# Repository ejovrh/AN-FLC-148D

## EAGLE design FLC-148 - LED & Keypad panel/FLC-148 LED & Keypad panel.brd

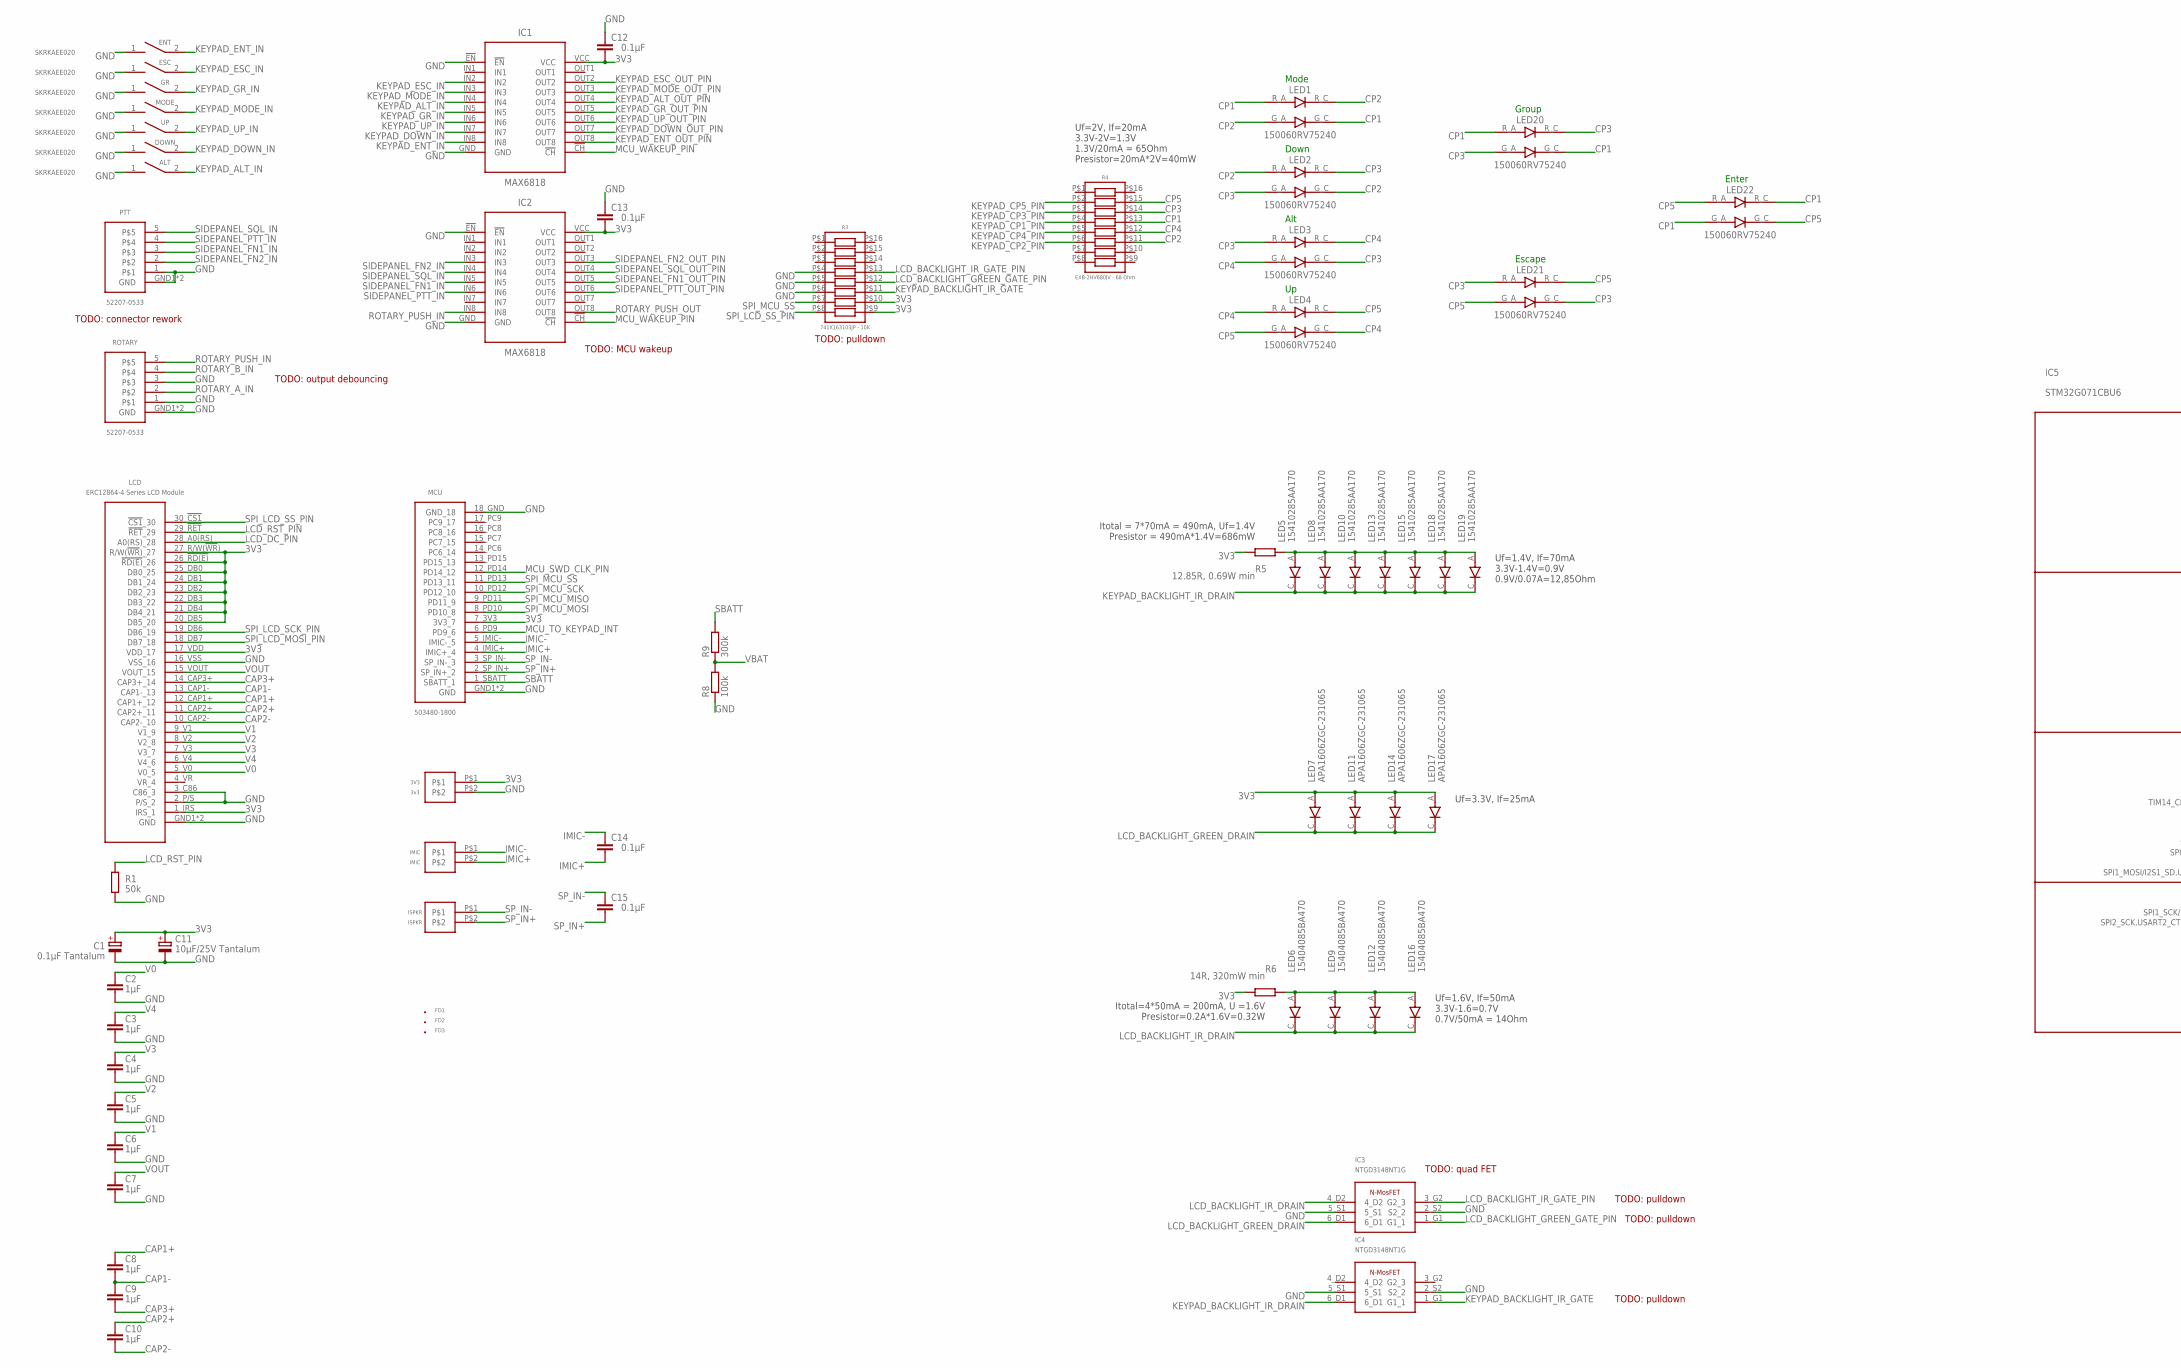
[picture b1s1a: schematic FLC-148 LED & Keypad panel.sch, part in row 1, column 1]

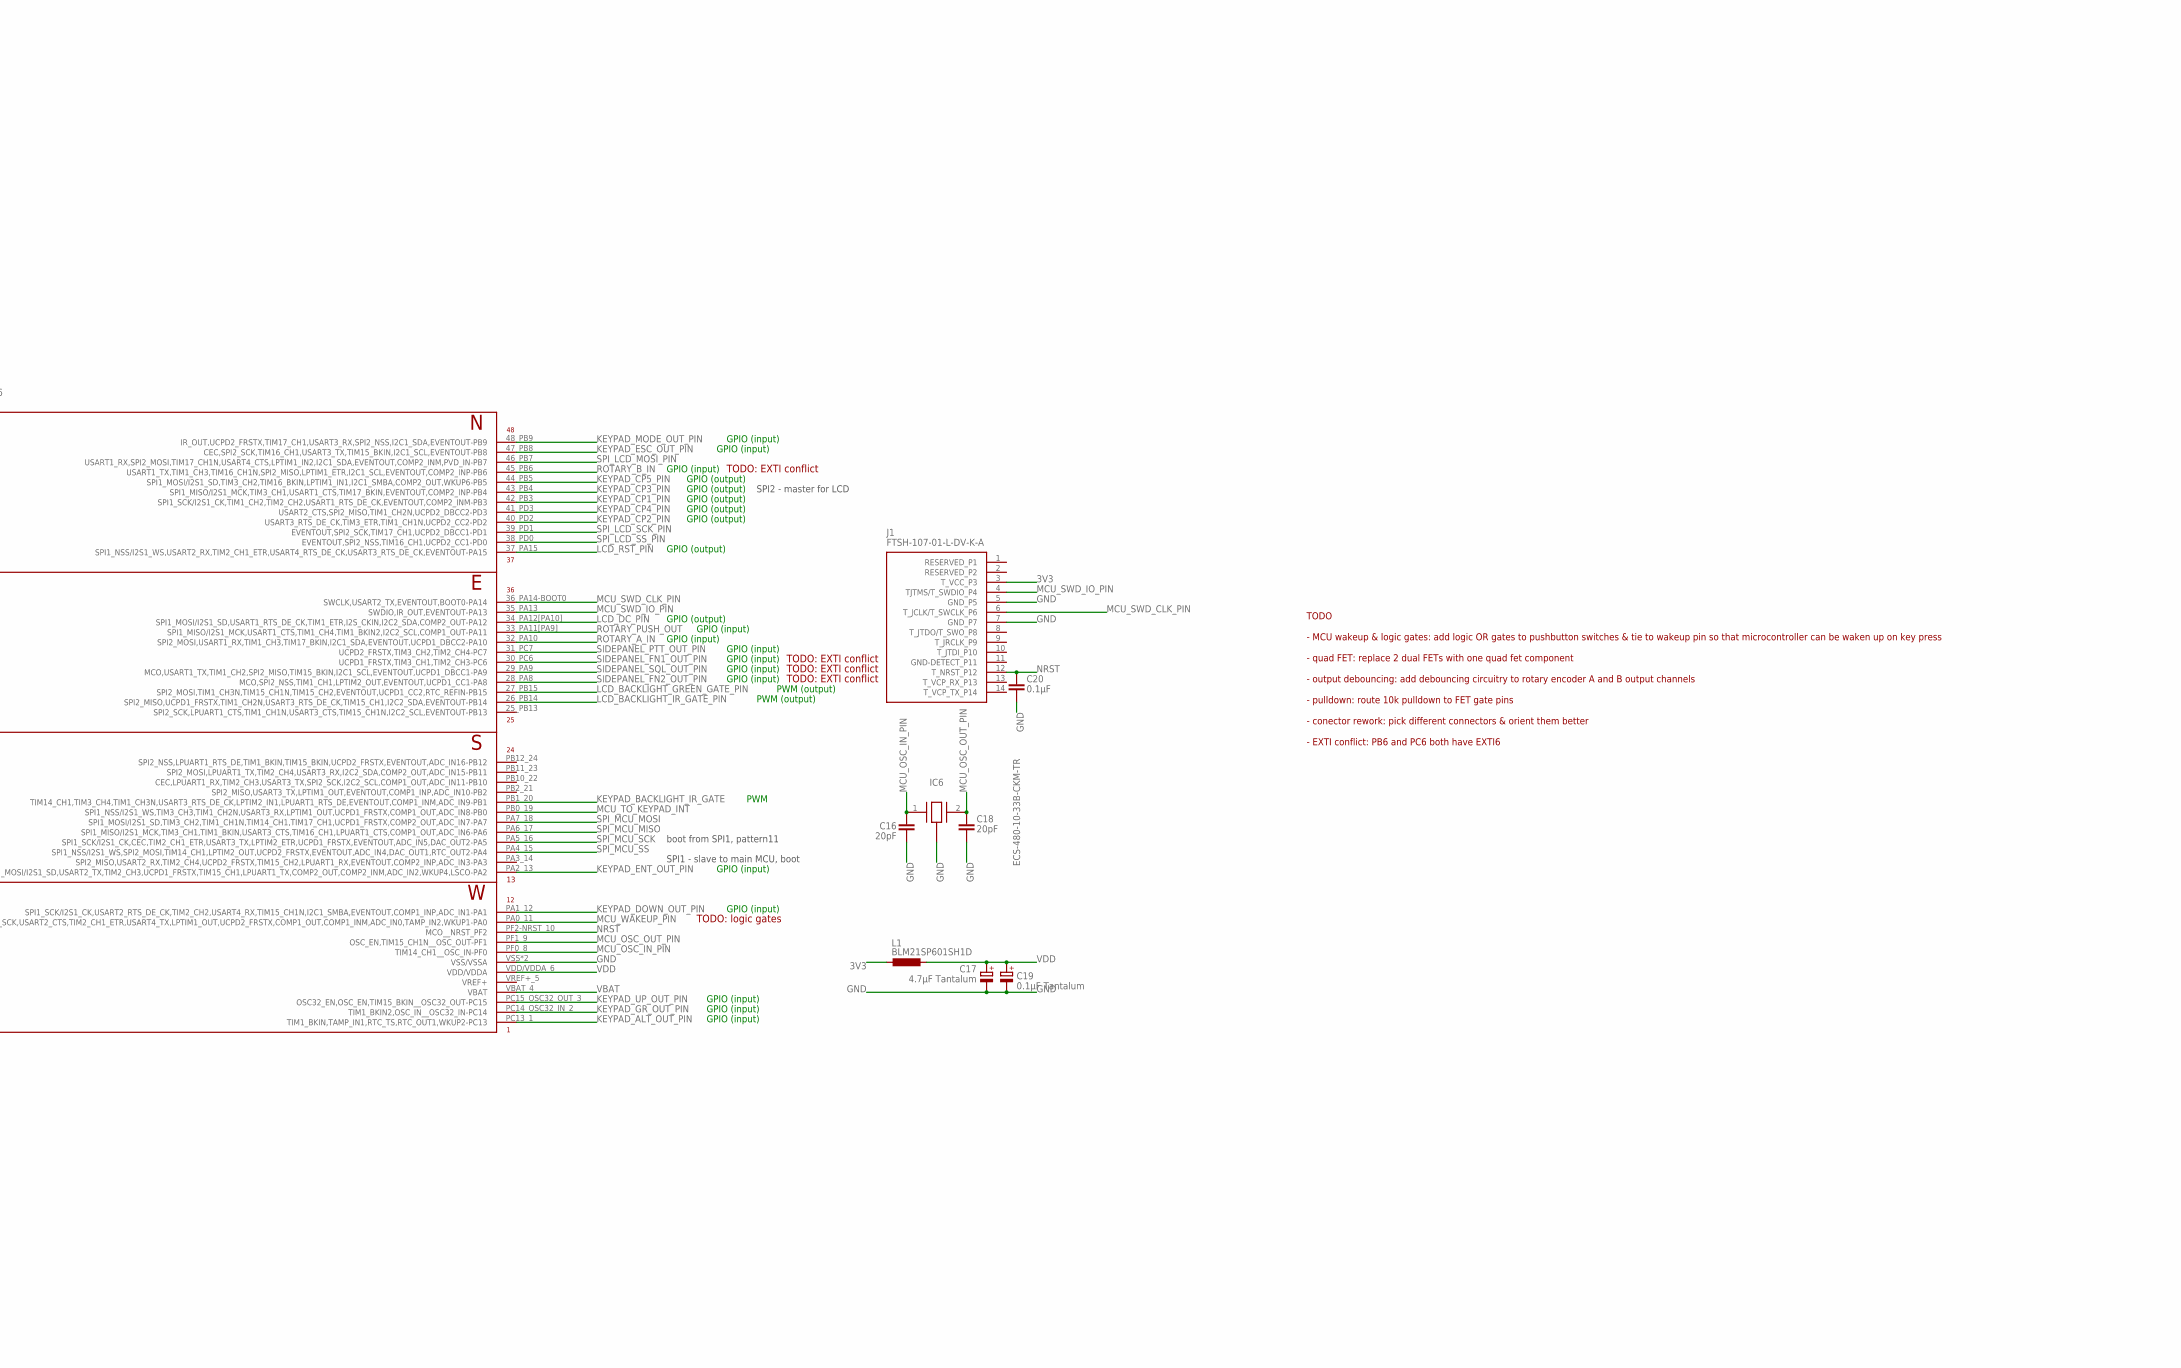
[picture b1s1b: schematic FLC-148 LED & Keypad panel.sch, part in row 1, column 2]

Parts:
3V3: 3v3; SMD
ALT: SKRKAEE020; SMD
C1, C19: 0.1μF Tantalum; SMC_A
C2, C3, C4, C5, C6, C7, C8, C9, C10: 1μF; C0402
C11: 10μF/25V Tantalum; SMC_B
C12, C13, C14, C15, C20: 0.1μF; C0402
C16, C18: 20pF; C0402
C17: 4.7μF Tantalum; SMC_A
DOWN: SKRKAEE020; SMD
ENT: SKRKAEE020; SMD
ESC: SKRKAEE020; SMD
FD1, FD2, FD3: FID_20MIL_P; FID_020_P
GR: SKRKAEE020; SMD
IC1, IC2: MAX6818; TSSOP20
IC3, IC4: NTGD3148NT1G; TSOP-6
IC5: STM32G071CBU6; UFQFPN48
IC6: ECS-480-10-33B-CKM-TR; 3.2X2.5MM
IMIC: IMIC; SMD
ISPKR: ISPKR; SMD
J1: FTSH-107-01-L-DV-K-A; FTSH10701LDVKA
L1: BLM21SP601SH1D; L2012C
LCD: ERC12864-4 Series LCD Module; SMD
LED1, LED2, LED3, LED4, LED20, LED21, LED22: 150060RV75240; SMD
LED5, LED8, LED10, LED13, LED15, LED18, LED19: 15410285AA170; 1002
LED6, LED9, LED12, LED16: 15404085BA470; 0402
LED7, LED11, LED14, LED17: APA1606ZGC-231065; 0605
MCU: 503480-1800; 5034801800-MOTHERBOARD<->LCD-PANEL
MODE: SKRKAEE020; SMD
PTT: 52207-0533; SMD
R1: 50k; R0402
R3: 741X163103JP - 10K; SMD
R4: EXB-2HV680JV - 68 Ohm; SMD
R5: 12.85R, 0.69W min; R1206
R6: 14R, 320mW min; R0805
R8: 100k; R0402
R9: 300k; R0402
ROTARY: 52207-0533; SMD
UP: SKRKAEE020; SMD

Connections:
3V3: 3V3.P$1, C1.+, C11.+, C12.2, C13.2, IC1.VCC, IC2.VCC, J1.3 (T_VCC_P3), L1.2, LCD.1_IRS (IRS_1), LCD.17_VDD (VDD_17), LCD.20_DB5 (DB5_20), LCD.21_DB4 (DB4_21), LCD.22_DB3 (DB3_22), LCD.23_DB2 (DB2_23), LCD.24_DB1 (DB1_24), LCD.25_DB0 (DB0_25), LCD.26_!RD(E)! (!RD(E)!_26), LCD.27_R/W(!WR!) (R/W(!WR!)_27), LED7.A, LED11.A, LED14.A, LED17.A, MCU.7_3V3 (3V3_7), R3.P$9, R3.P$10, R5.1, R6.1
CAP1+: C8.1, LCD.12_CAP1+ (CAP1+_12)
CAP1-: C8.2, C9.1, LCD.13_CAP1- (CAP1-_13)
CAP2+: C10.1, LCD.11_CAP2+ (CAP2+_11)
CAP2-: C10.2, LCD.10_CAP2- (CAP2-_10)
CAP3+: C9.2, LCD.14_CAP3+ (CAP3+_14)
CP1: LED1.G_C, LED1.R_A, LED20.G_C, LED20.R_A, LED22.G_A, LED22.R_C, R4.P$13
CP2: LED1.G_A, LED1.R_C, LED2.G_C, LED2.R_A, R4.P$11
CP3: LED2.G_A, LED2.R_C, LED3.G_C, LED3.R_A, LED20.G_A, LED20.R_C, LED21.G_C, LED21.R_A, R4.P$14
CP4: LED3.G_A, LED3.R_C, LED4.G_C, LED4.R_A, R4.P$12
CP5: LED4.G_A, LED4.R_C, LED21.G_A, LED21.R_C, LED22.G_C, LED22.R_A, R4.P$15
GND: 3V3.P$2, ALT.1, C1.-, C2.2, C3.2, C4.2, C5.2, C6.2, C7.2, C11.-, C12.1, C13.1, C16.2, C17.-, C18.2, C19.-, C20.2, DOWN.1, ENT.1, ESC.1, GR.1, IC1.!EN!, IC1.GND, IC2.!EN!, IC2.GND, IC3.2_S2 (S2_2), IC3.5_S1, IC4.2_S2 (S2_2), IC4.5_S1, IC5.VSS (VSS/VSSA), IC5.VSS/VSSA_7 (VSS/VSSA), IC6.GND1 (GND), IC6.GND2 (GND), J1.5 (GND_P5), J1.7 (GND_P7), LCD.2_P/S (P/S_2), LCD.3_C86 (C86_3), LCD.16_VSS (VSS_16), LCD.GND1 (GND), LCD.GND2 (GND), MCU.18_GND (GND_18), MCU.GND1 (GND), MCU.GND2 (GND), MODE.1, PTT.1, PTT.GND1 (GND), PTT.GND2 (GND), R1.1, R3.P$4, R3.P$5, R3.P$6, R8.1, ROTARY.1, ROTARY.3, ROTARY.GND1 (GND), ROTARY.GND2 (GND), UP.1
IMIC+: C14.2, IMIC.P$2, MCU.4_IMIC+ (IMIC+_4)
IMIC-: C14.1, IMIC.P$1, MCU.5_IMIC- (IMIC-_5)
IR_ANODE: LED6.A, LED9.A, LED12.A, LED16.A, R6.2
KEYPAD_ALT_IN: ALT.2, IC1.IN4
KEYPAD_ALT_OUT_PIN: IC1.OUT4, IC5.PC13_1 (TIM1_BKIN,TAMP_IN1,RTC_TS,RTC_OUT1,WKUP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)
KEYPAD_BACKLIGHT_IR_DRAIN: IC4.6_D1, LED5.C, LED8.C, LED10.C, LED13.C, LED15.C, LED18.C, LED19.C
KEYPAD_BACKLIGHT_IR_GATE: IC4.1_G1 (G1_1), IC5.PB1_20 (TIM14_CH1,TIM3_CH4,TIM1_CH3N,USART3_RTS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), R3.P$11
KEYPAD_CP1_PIN: IC5.42_PB3 (SPI1_SCK/I2S1_CK,TIM1_CH2,TIM2_CH2,USAR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), R4.P$4
KEYPAD_CP2_PIN: IC5.40_PD2 (USART3_RTS_DE_CK,TIM3_ETR,TIM1_CH1N,UCP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), R4.P$6
KEYPAD_CP3_PIN: IC5.43_PB4 (SPI1_MISO/I2S1_MCK,TIM3_CH1,USART1_CTS,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), R4.P$3
KEYPAD_CP4_PIN: IC5.41_PD3 (USART2_CTS,SPI2_MISO,TIM1_CH2N,UCPD2_DB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), R4.P$5
KEYPAD_CP5_PIN: IC5.44_PB5 (SPI1_MOSI/I2S1_SD,TIM3_CH2,TIM16_BKIN,L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), R4.P$2
KEYPAD_DOWN_IN: DOWN.2, IC1.IN7
KEYPAD_DOWN_OUT_PIN: IC1.OUT7, IC5.PA1_12 (SPI1_SCK/I2S1_CK,USART2_RTS_DE_CK,TIM2_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)
KEYPAD_ENT_IN: ENT.2, IC1.IN8
KEYPAD_ENT_OUT_PIN: IC1.OUT8, IC5.PA2_13 (SPI1_MOSI/I2S1_SD,USART2_TX,TIM2_CH3,UC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)
KEYPAD_ESC_IN: ESC.2, IC1.IN2
KEYPAD_ESC_OUT_PIN: IC1.OUT2, IC5.47_PB8 (CEC,SPI2_SCK,TIM16_CH1,USART3_TX,TIM15_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)
KEYPAD_GR_IN: GR.2, IC1.IN5
KEYPAD_GR_OUT_PIN: IC1.OUT5, IC5.PC14_OSC32_IN_2 (TIM1_BKIN2,OSC_IN__OSC32_IN-PC14)
KEYPAD_IR_LED_A: LED5.A, LED8.A, LED10.A, LED13.A, LED15.A, LED18.A, LED19.A, R5.2
KEYPAD_MODE_IN: IC1.IN3, MODE.2
KEYPAD_MODE_OUT_PIN: IC1.OUT3, IC5.48_PB9 (IR_OUT,UCPD2_FRSTX,TIM17_CH1,USART3_RX,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)
KEYPAD_UP_IN: IC1.IN6, UP.2
KEYPAD_UP_OUT_PIN: IC1.OUT6, IC5.PC15_OSC32_OUT_3 (OSC32_EN,OSC_EN,TIM15_BKIN__OSC32_OUT-P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)
LCD_BACKLIGHT_GREEN_DRAIN: IC3.6_D1, LED7.C, LED11.C, LED14.C, LED17.C
LCD_BACKLIGHT_GREEN_GATE_PIN: IC3.1_G1 (G1_1), IC5.27_PB15 (SPI2_MOSI,TIM1_CH3N,TIM15_CH1N,TIM15_CH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), R3.P$12
LCD_BACKLIGHT_IR_DRAIN: IC3.4_D2, LED6.C, LED9.C, LED12.C, LED16.C
LCD_BACKLIGHT_IR_GATE_PIN: IC3.3_G2 (G2_3), IC5.26_PB14 (SPI2_MISO,UCPD1_FRSTX,TIM1_CH2N,USART3_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), R3.P$13
LCD_DC_PIN: IC5.34_PA12[PA10] (SPI1_MOSI/I2S1_SD,USART1_RTS_DE_CK,TIM1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), LCD.28_A0(RS) (A0(RS)_28)
LCD_RST_PIN: IC5.37_PA15 (SPI1_NSS/I2S1_WS,USART2_RX,TIM2_CH1_ETR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), LCD.29_!RET! (!RET!_29), R1.2
MCU_OSC_IN_PIN: C16.1, IC5.PF0_8 (TIM14_CH1__OSC_IN-PF0), IC6.1
MCU_OSC_OUT_PIN: C18.1, IC5.PF1_9 (OSC_EN,TIM15_CH1N__OSC_OUT-PF1), IC6.2
MCU_SWD_CLK_PIN: IC5.36_PA14-BOOT0 (SWCLK,USART2_TX,EVENTOUT,BOOT0-PA14), J1.6 (T_JCLK/T_SWCLK_P6), MCU.12_PD14 (PD14_12)
MCU_SWD_IO_PIN: IC5.35_PA13 (SWDIO,IR_OUT,EVENTOUT-PA13), J1.4 (TJTMS/T_SWDIO_P4)
MCU_TO_KEYPAD_INT: IC5.PB0_19 (SPI1_NSS/I2S1_WS,TIM3_CH3,TIM1_CH2N,USA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), MCU.6_PD9 (PD9_6)
MCU_WAKEUP_PIN: IC1.!CH!, IC2.!CH!, IC5.PA0_11 (SPI2_SCK,USART2_CTS,TIM2_CH1_ETR,USART4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)
NRST: C20.1, IC5.PF2-NRST_10 (MCO__NRST_PF2), J1.12 (T_NRST_P12)
ROTARY_A_IN: IC5.32_PA10 (SPI2_MOSI,USART1_RX,TIM1_CH3,TIM17_BKIN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), ROTARY.2
ROTARY_B_IN: IC5.45_PB6 (USART1_TX,TIM1_CH3,TIM16_CH1N,SPI2_MISO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), ROTARY.4
ROTARY_PUSH_IN: IC2.IN8, ROTARY.5
ROTARY_PUSH_OUT: IC2.OUT8, IC5.33_PA11[PA9] (SPI1_MISO/I2S1_MCK,USART1_CTS,TIM1_CH4,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)
SBATT: MCU.1_SBATT (SBATT_1), R9.2
SIDEPANEL_FN1_IN: IC2.IN5, PTT.3
SIDEPANEL_FN1_OUT_PIN: IC2.OUT5, IC5.30_PC6 (UCPD1_FRSTX,TIM3_CH1,TIM2_CH3-PC6)
SIDEPANEL_FN2_IN: IC2.IN3, PTT.2
SIDEPANEL_FN2_OUT_PIN: IC2.OUT3, IC5.28_PA8 (MCO,SPI2_NSS,TIM1_CH1,LPTIM2_OUT,EVENTO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)
SIDEPANEL_PTT_IN: IC2.IN6, PTT.4
SIDEPANEL_PTT_OUT_PIN: IC2.OUT6, IC5.31_PC7 (UCPD2_FRSTX,TIM3_CH2,TIM2_CH4-PC7)
SIDEPANEL_SQL_IN: IC2.IN4, PTT.5
SIDEPANEL_SQL_OUT_PIN: IC2.OUT4, IC5.29_PA9 (MCO,USART1_TX,TIM1_CH2,SPI2_MISO,TIM15_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)
SPI_LCD_MOSI_PIN: IC5.46_PB7 (USART1_RX,SPI2_MOSI,TIM17_CH1N,USART4_C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), LCD.18_DB7 (DB7_18)
SPI_LCD_SCK_PIN: IC5.39_PD1 (EVENTOUT,SPI2_SCK,TIM17_CH1,UCPD2_DBCC1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), LCD.19_DB6 (DB6_19)
SPI_LCD_SS_PIN: IC5.38_PD0 (EVENTOUT,SPI2_NSS,TIM16_CH1,UCPD2_CC1-P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), LCD.30_!CS1! (!CS1!_30), R3.P$8
SPI_MCU_MISO: IC5.PA6_17 (SPI1_MISO/I2S1_MCK,TIM3_CH1,TIM1_BKIN,U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), MCU.9_PD11 (PD11_9)
SPI_MCU_MOSI: IC5.PA7_18 (SPI1_MOSI/I2S1_SD,TIM3_CH2,TIM1_CH1N,TI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), MCU.8_PD10 (PD10_8)
SPI_MCU_SCK: IC5.PA5_16 (SPI1_SCK/I2S1_CK,CEC,TIM2_CH1_ETR,USART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), MCU.10_PD12 (PD12_10)
SPI_MCU_SS: IC5.PA4_15 (SPI1_NSS/I2S1_WS,SPI2_MOSI,TIM14_CH1,LP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), MCU.11_PD13 (PD13_11), R3.P$7
SP_IN+: C15.2, ISPKR.P$2, MCU.2_SP_IN+ (SP_IN+_2)
SP_IN-: C15.1, ISPKR.P$1, MCU.3_SP_IN- (SP_IN-_3)
V0: C2.1, LCD.5_V0 (V0_5)
V1: C6.1, LCD.9_V1 (V1_9)
V2: C5.1, LCD.8_V2 (V2_8)
V3: C4.1, LCD.7_V3 (V3_7)
V4: C3.1, LCD.6_V4 (V4_6)
VBAT: IC5.VBAT_4 (VBAT), R8.2, R9.1
VDD: C17.+, C19.+, IC5.VDD/VDDA_6 (VDD/VDDA), L1.1
VOUT: C7.1, LCD.15_VOUT (VOUT_15)

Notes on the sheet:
Uf=2V, If=20mA 3.3V-2V=1.3V 1.3V/20mA = 65Ohm Presistor=20mA*2V=40mW
SPI1 - slave to main MCU, boot
boot from SPI1, pattern11
Uf=1.6V, If=50mA 3.3V-1.6=0.7V 0.7V/50mA = 14Ohm
Uf=3.3V, If=25mA
Uf=1.4V, If=70mA 3.3V-1.4V=0.9V 0.9V/0.07A=12,85Ohm
SPI2 - master for LCD
Itotal = 7*70mA = 490mA, Uf=1.4V Presistor = 490mA*1.4V=686mW
Itotal=4*50mA = 200mA, U =1.6V Presistor=0.2A*1.6V=0.32W
PWM (output)
GPIO (input)
PWM
GPIO (output)
TODO: quad FET
TODO: logic gates
TODO - MCU wakeup & logic gates: add logic OR gates to pushbutton switches & tie to wakeup pin so that microcontroller can be waken up on key press - quad FET: replace 2 dual FETs with one quad fet component - output debouncing: add debouncing circuitry to rotary encoder A and B output channels - p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
TODO: output debouncing
TODO: pulldown
TODO: connector rework
TODO: MCU wakeup
TODO: EXTI conflict
Mode
Down
Alt
Group
Escape
Enter

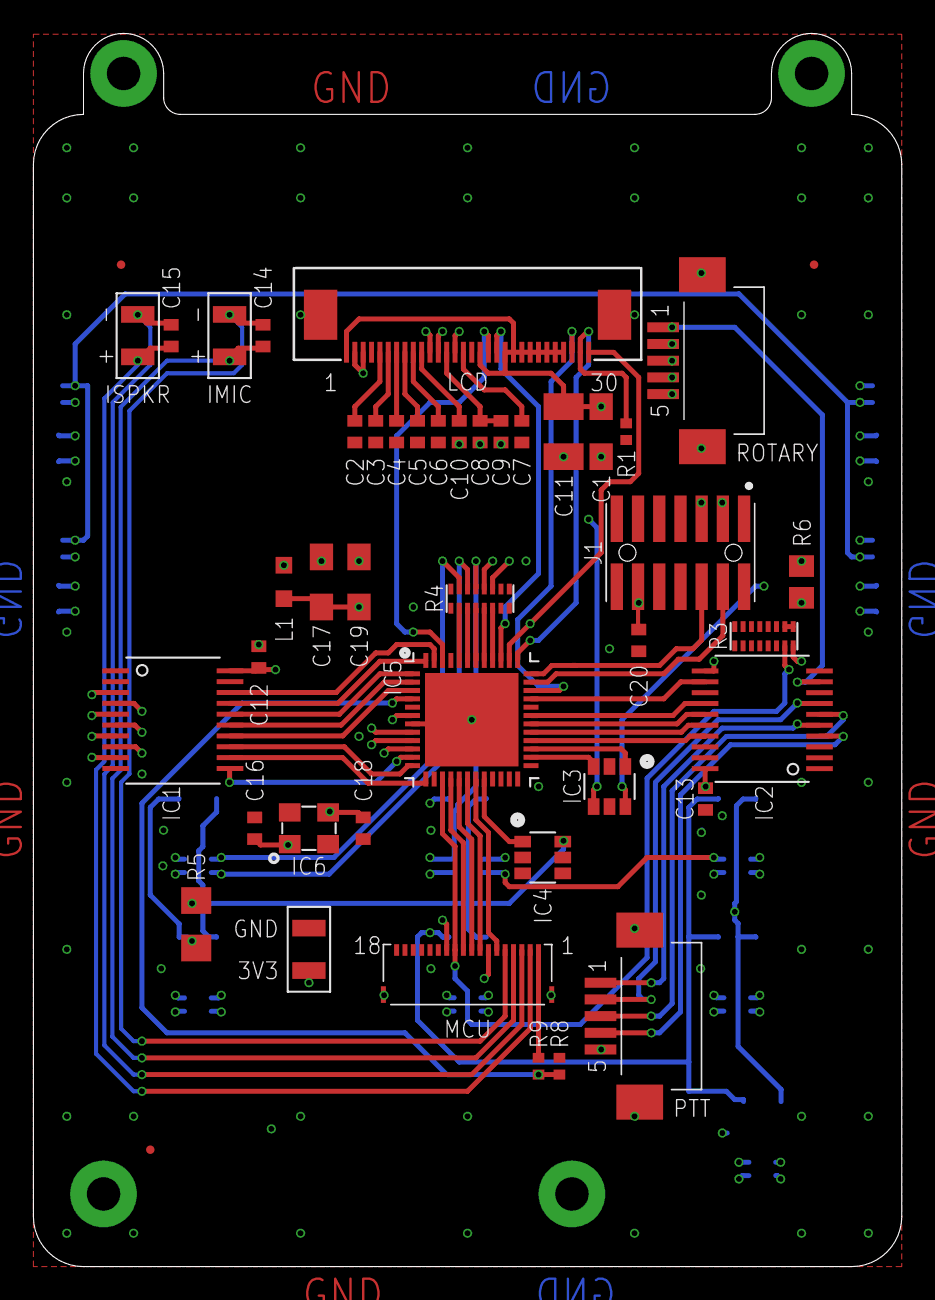
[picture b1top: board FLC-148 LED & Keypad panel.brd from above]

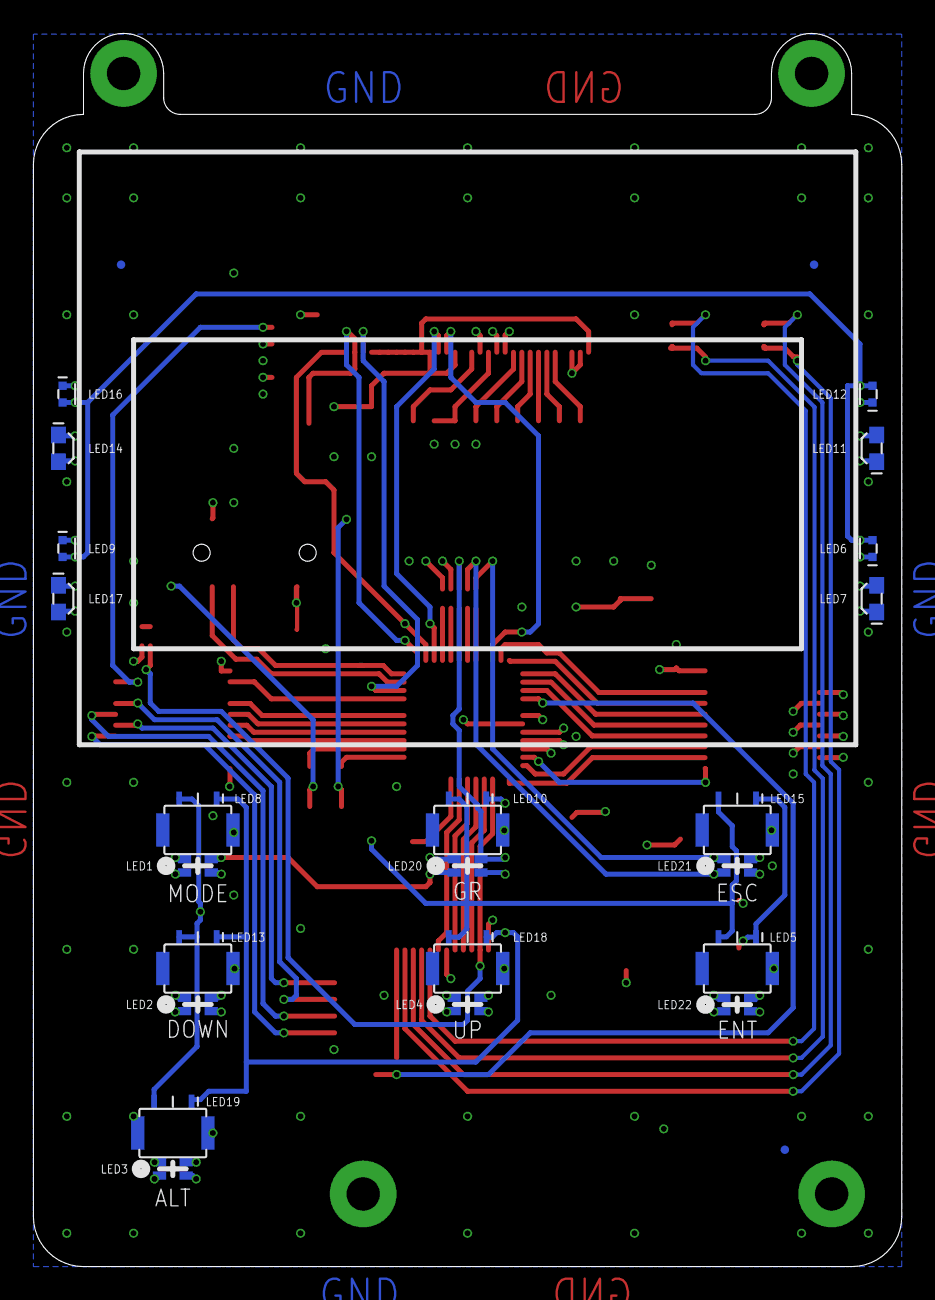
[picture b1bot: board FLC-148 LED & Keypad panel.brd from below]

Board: 4 copper layers, 52.0 x 73.8 mm, 74 parts (29 on the bottom side), 80 nets.

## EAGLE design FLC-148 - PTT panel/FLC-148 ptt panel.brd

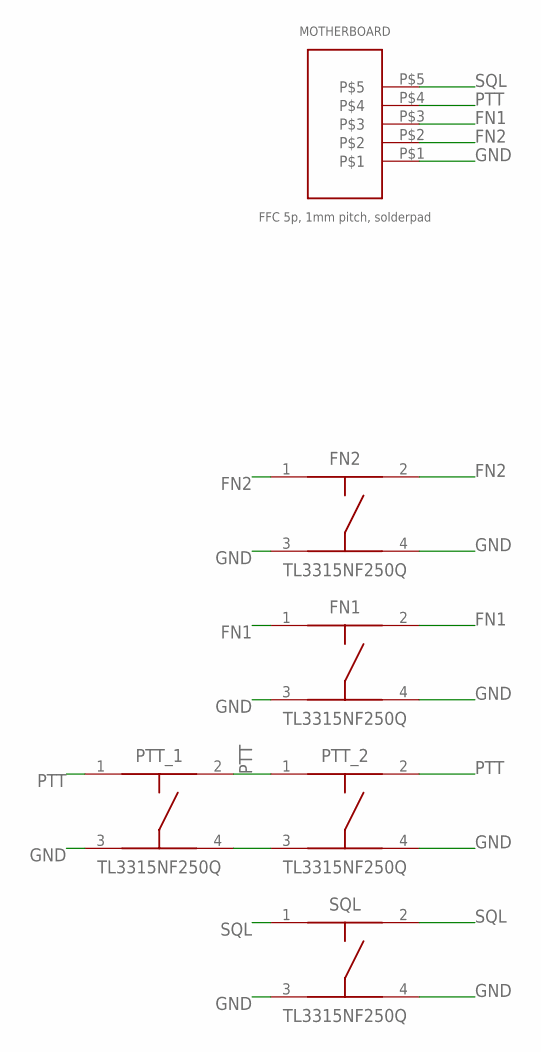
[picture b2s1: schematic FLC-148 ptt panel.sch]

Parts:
FN1, FN2: TL3315NF250Q; SMT
MOTHERBOARD: FFC 5p, 1mm pitch, solderpad; FFC_1MM_5P
PTT_1, PTT_2: TL3315NF250Q; SMT
SQL: TL3315NF250Q; SMT

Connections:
FN1: FN1.1, FN1.2, MOTHERBOARD.P$3
FN2: FN2.1, FN2.2, MOTHERBOARD.P$2
GND: FN1.3, FN1.4, FN2.3, FN2.4, MOTHERBOARD.P$1, PTT_1.3, PTT_1.4, PTT_2.3, PTT_2.4, SQL.3, SQL.4
PTT: MOTHERBOARD.P$4, PTT_1.1, PTT_1.2, PTT_2.1, PTT_2.2
SQL: MOTHERBOARD.P$5, SQL.1, SQL.2

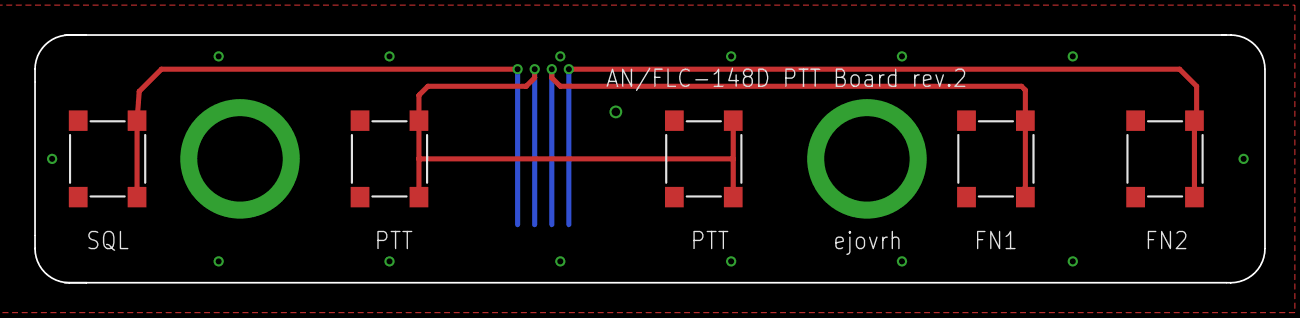
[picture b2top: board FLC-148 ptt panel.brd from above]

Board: 2 copper layers, 72.0 x 14.5 mm, 6 parts (1 on the bottom side), 5 nets.

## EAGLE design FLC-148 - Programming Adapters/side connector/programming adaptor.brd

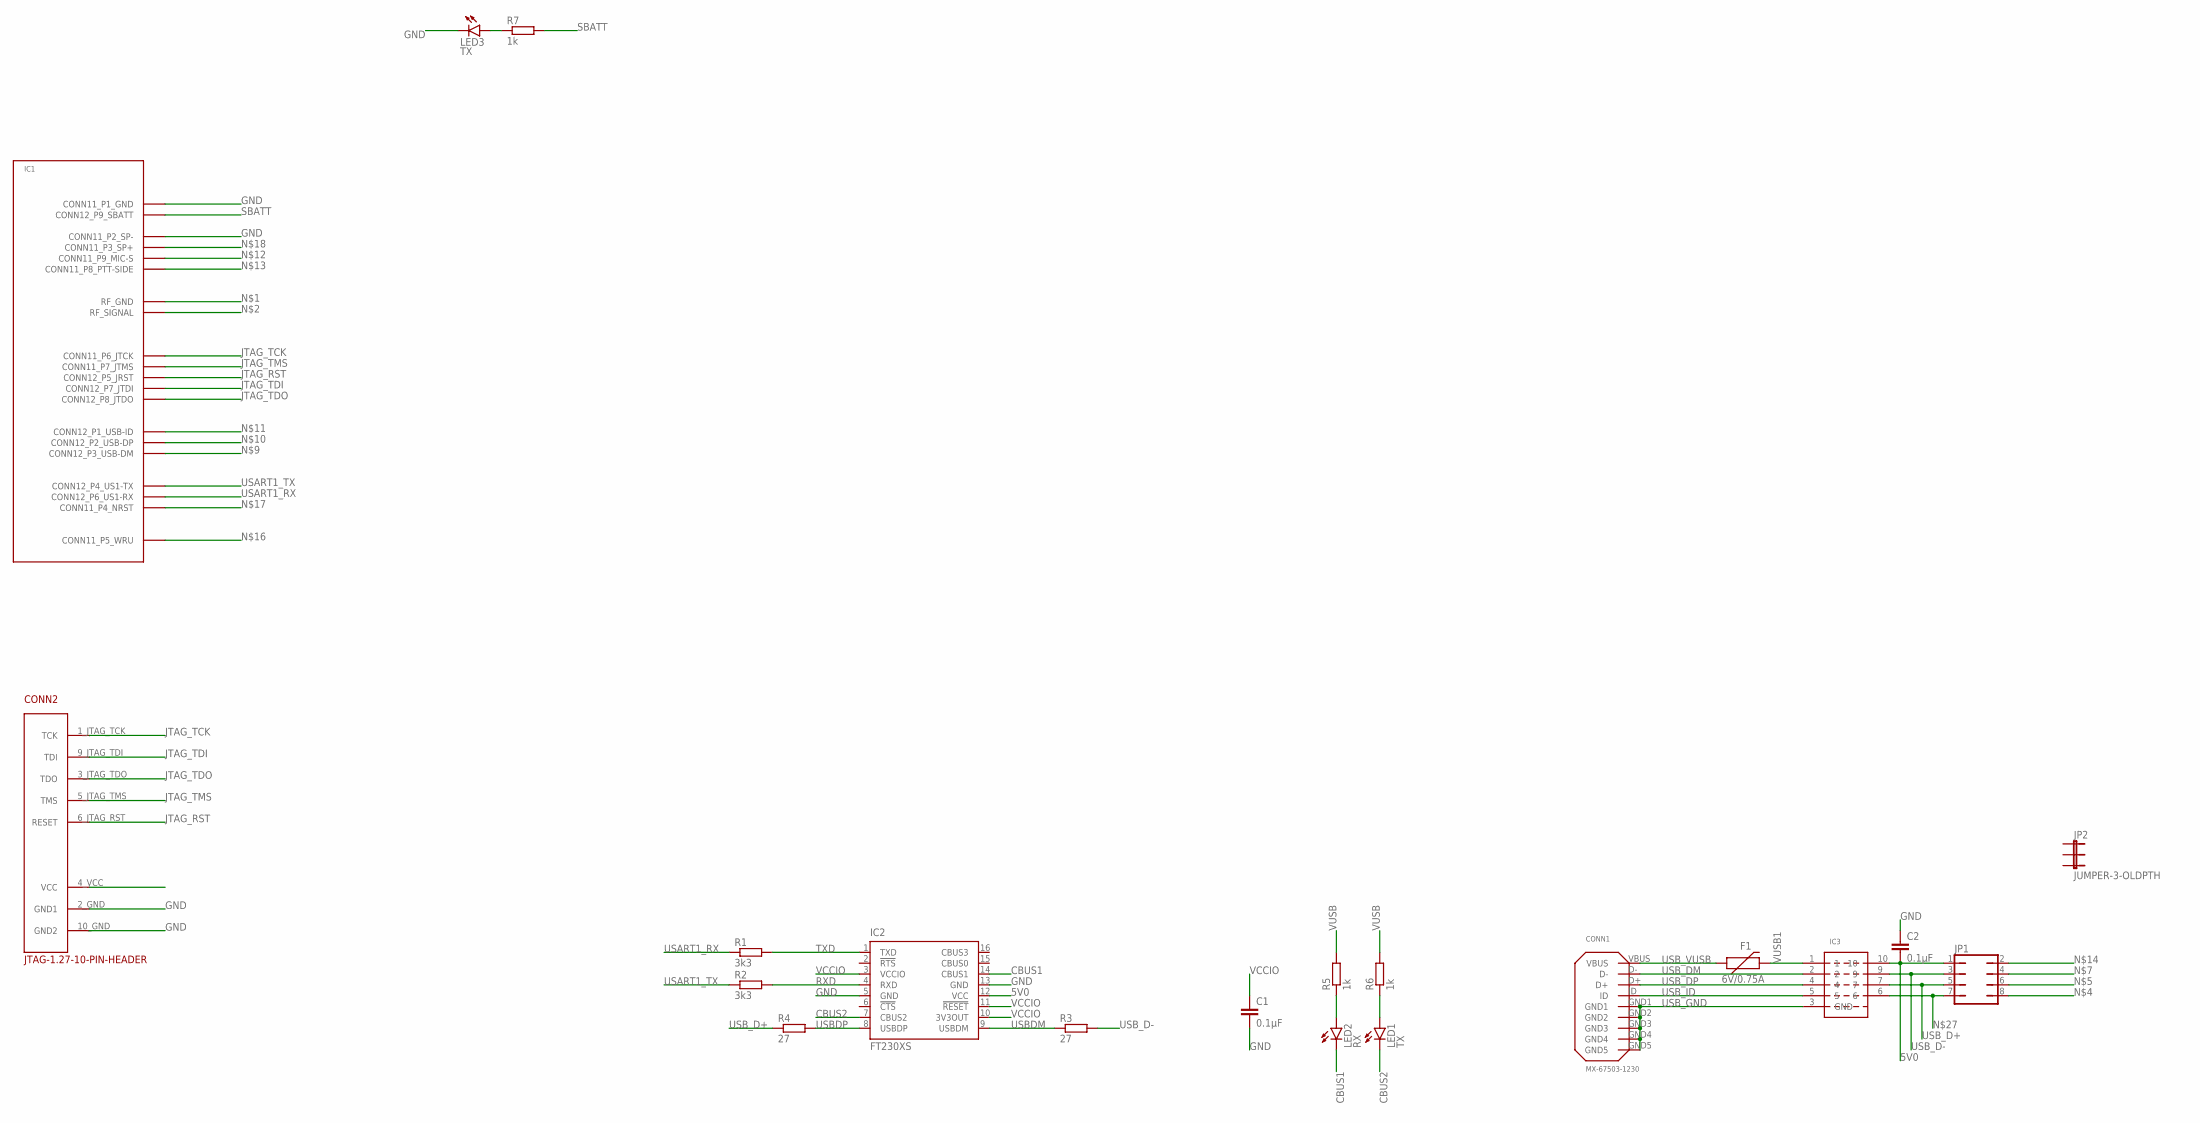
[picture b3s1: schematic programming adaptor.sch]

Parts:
C1, C2: 0.1µF; C0805
CONN1: MX-67503-1230; SMT
CONN2: JTAG-1.27-10-PIN-HEADER; TH-JTAG
F1: 6V/0.75A; 1206
IC1: FLC-148; TH
IC2: FT230XS; SSOP16
IC3: SP3012-04UTG; μDFN-10
JP1: JP4Q
JP2: JUMPER-3-OLDPTH; 1X03
LED1, LED3: TX; CHIPLED_1206
LED2: RX; CHIPLED_1206
R1, R2: 3k3; R0805
R3, R4: 27; R0805
R5, R6, R7: 1k; R0805

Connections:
5V0: C2.2, IC2.12 (VCC), IC3.10, JP1.1
CBUS1: IC2.14 (CBUS1), LED2.C
CBUS2: IC2.7 (CBUS2), LED1.C
GND: C1.2, C2.1, CONN2.2_GND (GND1), CONN2.10_GND (GND2), IC1.CONN11_P1 (CONN11_P1_GND), IC1.CONN11_P2 (CONN11_P2_SP-), IC2.5 (GND), IC2.13 (GND), LED3.C
JTAG_RST: CONN2.6_JTAG_RST (RESET), IC1.CONN12_P5 (CONN12_P5_JRST)
JTAG_TCK: CONN2.1_JTAG_TCK (TCK), IC1.CONN11_P6 (CONN11_P6_JTCK)
JTAG_TDI: CONN2.9_JTAG_TDI (TDI), IC1.CONN12_P7 (CONN12_P7_JTDI)
JTAG_TDO: CONN2.3_JTAG_TDO (TDO), IC1.CONN12_P8 (CONN12_P8_JTDO)
JTAG_TMS: CONN2.5_JTAG_TMS (TMS), IC1.CONN11_P7 (CONN11_P7_JTMS)
unnamed: LED2.A, R5.1
unnamed: LED1.A, R6.1
unnamed: LED3.A, R7.1
unnamed: IC3.6, JP1.7
RXD: IC2.4 (RXD), R2.2
SBATT: IC1.CONN12_P9 (CONN12_P9_SBATT), R7.2
TXD: IC2.1 (TXD), R1.2
USART1_RX: IC1.CONN12_P6 (CONN12_P6_US1-RX), R1.1
USART1_TX: IC1.CONN12_P4 (CONN12_P4_US1-TX), R2.1
USBDM: IC2.9 (USBDM), R3.1
USBDP: IC2.8 (USBDP), R4.2
USB_D+: IC3.7, JP1.5, R4.1
USB_D-: IC3.9, JP1.3, R3.2
USB_DM: CONN1.D-, IC3.2
USB_DP: CONN1.D+, IC3.4
USB_GND: CONN1.GND1, CONN1.GND2, CONN1.GND3, CONN1.GND4, CONN1.GND5, IC3.3 (GND)
USB_ID: CONN1.ID, IC3.5
USB_VUSB: CONN1.VBUS, F1.1
VCCIO: C1.1, IC2.3 (VCCIO), IC2.10 (3V3OUT), IC2.11 (!RESET)
VUSB: R5.2, R6.2
VUSB1: F1.2, IC3.1

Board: 2 copper layers, 20 parts (20 on the bottom side), 30 nets, no tracks yet.

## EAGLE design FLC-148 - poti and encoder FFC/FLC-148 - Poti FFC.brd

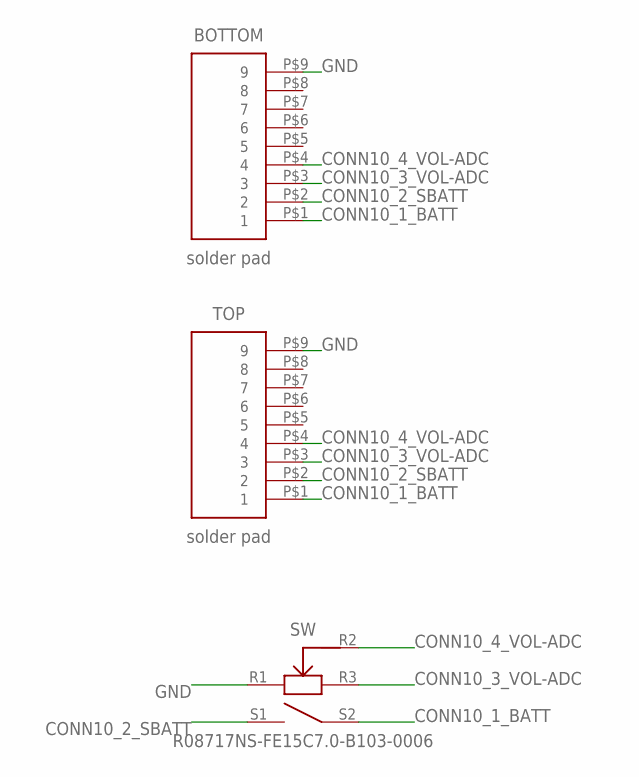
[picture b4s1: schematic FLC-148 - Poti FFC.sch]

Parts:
BOTTOM: solder pad; SMD
SW: R08717NS-FE15C7.0-B103-0006; TH
TOP: solder pad; SMD

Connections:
CONN10_1_BATT: BOTTOM.P$1 (1), SW.S2, TOP.P$1 (1)
CONN10_2_SBATT: BOTTOM.P$2 (2), SW.S1, TOP.P$2 (2)
CONN10_3_VOL-ADC: BOTTOM.P$3 (3), SW.R3, TOP.P$3 (3)
CONN10_4_VOL-ADC: BOTTOM.P$4 (4), SW.R2, TOP.P$4 (4)
GND: BOTTOM.P$9 (9), SW.R1, TOP.P$9 (9)

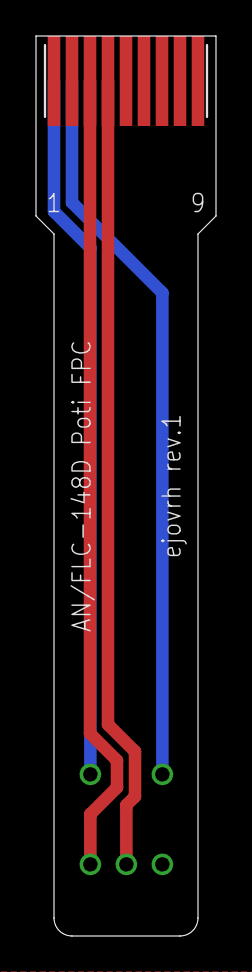
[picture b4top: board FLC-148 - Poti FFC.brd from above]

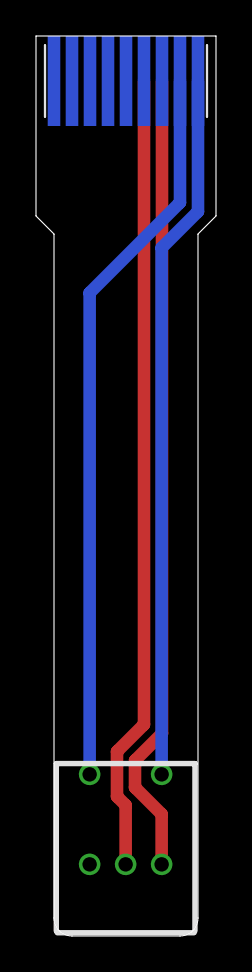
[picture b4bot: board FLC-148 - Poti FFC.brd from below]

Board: 2 copper layers, 10.0 x 50.0 mm, 3 parts (2 on the bottom side), 5 nets.

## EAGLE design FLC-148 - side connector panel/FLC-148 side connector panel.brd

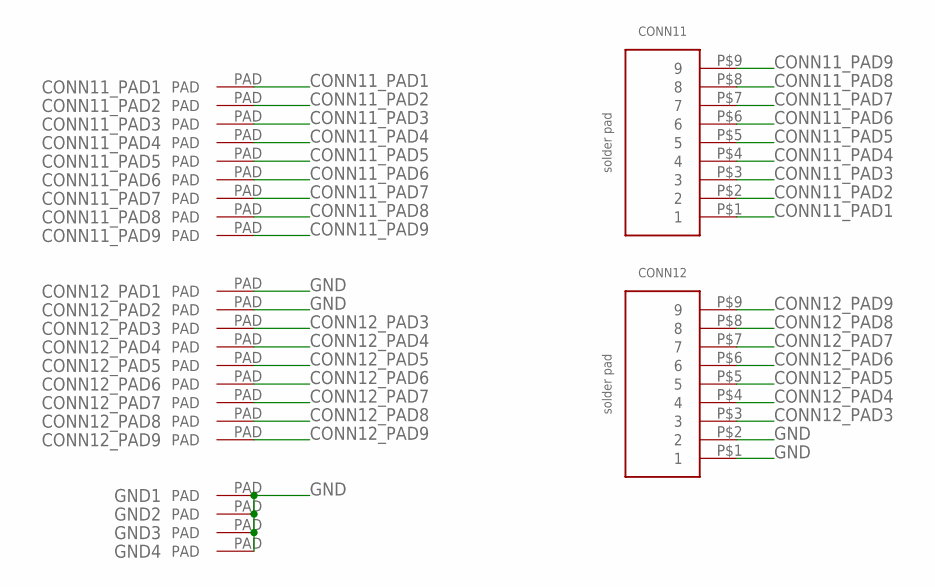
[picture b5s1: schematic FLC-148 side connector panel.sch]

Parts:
CONN11, CONN12: solder pad; FFC_1MM_9P
CONN11_PAD1, CONN11_PAD2, CONN11_PAD3, CONN11_PAD4, CONN11_PAD5, CONN11_PAD6, CONN11_PAD7, CONN11_PAD8, CONN11_PAD9, CONN12_PAD1, CONN12_PAD2, CONN12_PAD3, CONN12_PAD4, CONN12_PAD5, CONN12_PAD6, CONN12_PAD7, CONN12_PAD8, CONN12_PAD9: PAD
GND1, GND2, GND3, GND4: PAD

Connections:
CONN11_PAD1: CONN11.P$1 (1), CONN11_PAD1.PAD
CONN11_PAD2: CONN11.P$2 (2), CONN11_PAD2.PAD
CONN11_PAD3: CONN11.P$3 (3), CONN11_PAD3.PAD
CONN11_PAD4: CONN11.P$4 (4), CONN11_PAD4.PAD
CONN11_PAD5: CONN11.P$5 (5), CONN11_PAD5.PAD
CONN11_PAD6: CONN11.P$6 (6), CONN11_PAD6.PAD
CONN11_PAD7: CONN11.P$7 (7), CONN11_PAD7.PAD
CONN11_PAD8: CONN11.P$8 (8), CONN11_PAD8.PAD
CONN11_PAD9: CONN11.P$9 (9), CONN11_PAD9.PAD
CONN12_PAD3: CONN12.P$3 (3), CONN12_PAD3.PAD
CONN12_PAD4: CONN12.P$4 (4), CONN12_PAD4.PAD
CONN12_PAD5: CONN12.P$5 (5), CONN12_PAD5.PAD
CONN12_PAD6: CONN12.P$6 (6), CONN12_PAD6.PAD
CONN12_PAD7: CONN12.P$7 (7), CONN12_PAD7.PAD
CONN12_PAD8: CONN12.P$8 (8), CONN12_PAD8.PAD
CONN12_PAD9: CONN12.P$9 (9), CONN12_PAD9.PAD
GND: CONN12.P$1 (1), CONN12.P$2 (2), CONN12_PAD1.PAD, CONN12_PAD2.PAD, GND1.PAD, GND2.PAD, GND3.PAD, GND4.PAD

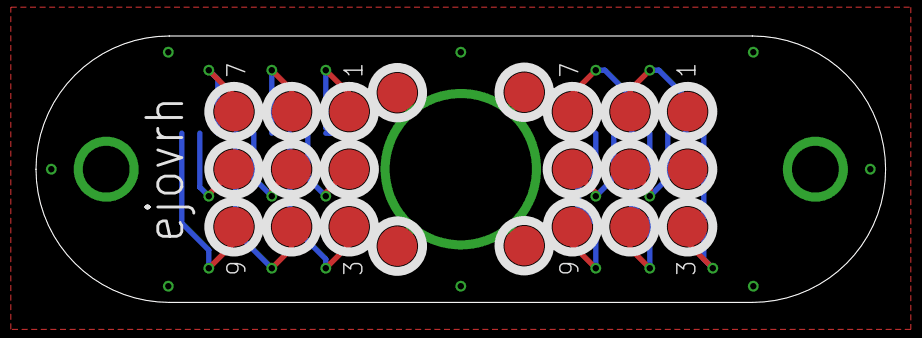
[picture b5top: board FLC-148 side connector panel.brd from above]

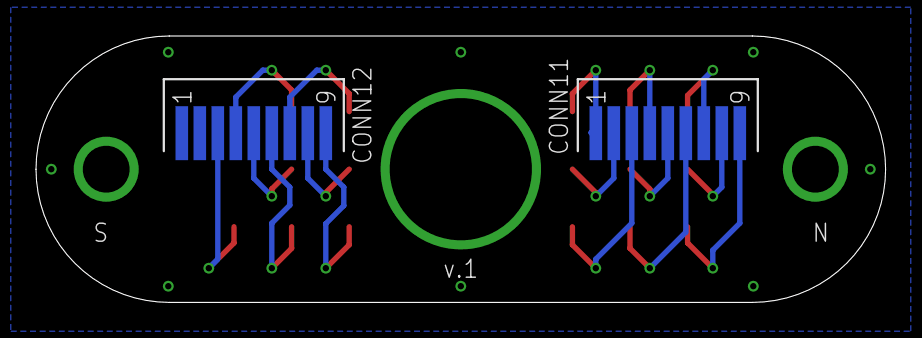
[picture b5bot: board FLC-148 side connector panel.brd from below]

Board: 2 copper layers, 47.2 x 14.8 mm, 24 parts (2 on the bottom side), 17 nets.

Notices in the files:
parts and their libraries:
SparkFun-Fuses: Licensing: Creative Commons ShareAlike 4.0 International - https://creativecommons.org/licenses/by-sa/4.0
